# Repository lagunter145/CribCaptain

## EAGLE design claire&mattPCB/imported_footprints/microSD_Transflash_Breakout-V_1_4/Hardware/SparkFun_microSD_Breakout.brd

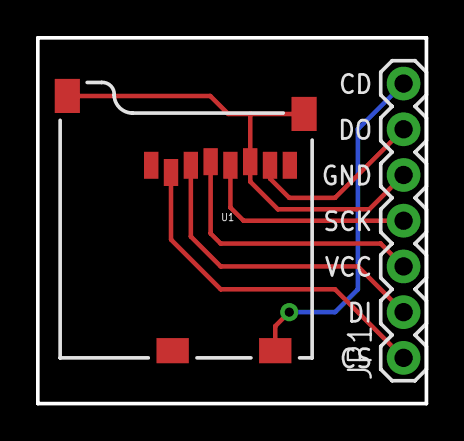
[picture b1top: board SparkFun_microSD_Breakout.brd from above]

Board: 2 copper layers, 21.6 x 20.3 mm, 3 parts (1 on the bottom side), 7 nets.

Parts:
JP1: 1X07
U1: microSD; MICRO-SD-SOCKET-PP
U$1: LOGO-SFENEW; SFE-NEW-WEBLOGO

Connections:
CD1: JP1.7, U1.CD2
CS: JP1.1, U1.2
DI: JP1.2, U1.3
DO: JP1.6, U1.7
GND: JP1.5, U1.6, U1.GND1, U1.GND2
SCK: JP1.4, U1.5
VCC: JP1.3, U1.4

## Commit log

2023-01-18 started pcb kicad project and added stm32 stuff to schematic
2023-01-18 started Eclipse project for code
2023-01-24 3.5 inch display without touch setup included in lcd.c
2023-01-25 t_irq added so that when user touches screen, it registers
2023-01-25 add to gitignore
2023-01-26 schematic for 2.8in touch display with all pins connected
2023-01-27 add language settings xml to gitignore
2023-01-27 Reading from SPI for display's touch
2023-01-30 create rfid files
2023-01-30 basic UART read/write functions, untested.
2023-01-31 copied over functions from Elechouse libraries
2023-02-01 schematics for keypad, lights, 7in display, separate SPI's for 2.8in
2023-02-01 trying different ways to implement touch display's comms on 1 SPI
2023-02-02 changed datatypes of functions
2023-02-03 added back waiting for RXNE bit to read
2023-02-05 SPI-40Pin controller touch added and keypad mod in pcb schematic
2023-02-06 ltspice simulation for sine to square wave converter
2023-02-06 LTSpice simulation for converting a sine to a square wave with same frequency
2023-02-06 wi-fi module, RFID scanner, sineToSquare converter, AC-DC converter
2023-02-06 footprints for IN5822 and RA8875
2023-02-06 removed github repo linking from RA8875 project
2023-02-06 SD Card Reader Schematic
2023-02-07 footprints for SD Card Reader
2023-02-07 4x4 keypad footprint
2023-02-07 linked 4x4 keypad footprint to schematic
2023-02-07 fixed receive() return type to uint
2023-02-08 rounded corner edge cuts and silkscreen for pin labels
2023-02-08 folder for hardware assembly, PN532 V3 RFID model
2023-02-08 2 separate SPI's for 2.8in TFT display and touch
2023-02-08 FillScreen algo adapted from Adafruit RA8775, not init
2023-02-08 minor changes
2023-02-09 initialize display
2023-02-09 ESP8266 footprint and ran electrical check
2023-02-09 organized schematic and separated power supply by modules and our design
2023-02-10 display not working, changed init, testing w arduino
2023-02-10 footprint for barrel jack adapter
2023-02-10 buck rectifier circuit (values wrong), changed how power flags were
2023-02-10 buck converter module cad
2023-02-11 voltage converter module footrints, all components have footprints, BOM
2023-02-11 generated netlist and fixed errors from PCB editing tool
2023-02-14 keypad 3D blueprint
2023-02-14 footprints for every component, pcb footprint layout
2023-02-14 v base casing blueprint
2023-02-14 TPS56325x schematic symbol and footprint
2023-02-15 RA8875 and ESP8266 updated footprints
2023-02-15 added 2.8in tft display in addition to 7in one
2023-02-17 Can read 1 RFID card passively
2023-02-21 micro sd connector schematic/footprint, lm324 footprint
2023-02-22 able to fill screen of display
2023-02-22 updated symbols to include pin names to get rid of ERC warnings
2023-02-22 PCB for 362 development board
2023-02-22 passed ERC and footprints assigned
2023-02-22 moved all 3D files of PCB into hardware assembly folder
2023-02-23 create byte transfer function
2023-02-24 SPI read function working
2023-02-24 initial PCB components, traces laid out with DRC passed
2023-02-24 1:1 footprint changes and layout modded to follow rules
2023-02-25 cleaned up code, touch polling works
2023-02-27 PCB version 2.0
2023-02-28 added text functions
2023-02-28 updated schematic with text descriptions for each block. Also, added 0 ohm resistor and 10 ohm current limiting resistor to pcb. Minor changes were made to the designed buck converter circuit.
2023-02-28 added fantabulous silkscreen names to the board (schmack dab in the middle)
2023-03-01 no DRC warnings
2023-03-08 added oscillator for micro
2023-03-08 added diodes pointing to where 5V outputs
2023-03-08 diodes and vias w labels added
2023-03-10 touch read moved to EXTI interrupt
2023-03-21 last commit before pulling - matthew
2023-03-21 pcb finalization
2023-03-22 wifi: added httprequest function and a semaphore system to timer 6. This will allow there to be delay between different AT commands. timesync: added a basic time system that can be displayed on the 7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
2023-03-24 color changing button!
2023-03-25 wifi: added a more refined http get request that has host header and can now interface with worldclockapi.com. Tried to parse information, but was struggling to read anything being recieved by PA10. 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
2023-03-25 wifi: resolved issue with wifi_getchar
2023-03-28 wifi: finished wifi-time demo (2/27/23) (Matthew and Philip)
2023-03-29 wifi: added second accuracy and fixed it counting to 60 seconds and 60 minutes (Matthew)
2023-03-29 rfid: began to write DMA access info (Matthew)
2023-03-29 wrote simple led main code to test pcb mirco (Matt)
2023-03-30 Add files via upload
    Keypad Stuff
2023-03-31 rfid: using a different module, the new dma code began to work. It works now with one card. The address for th CSELR register was fixed from 0x400202A0 to 0x400200A8 (Matthew and Philip)
2023-04-05 updated to properly read uid's into global array
    disable DMA after receiving a uid packet and writing another command to passive scan for another card. reenable after to prevent the command's ACK frame response from filling the uid buffer.
2023-04-05 working demo for checking off PCB Touch, wifi, timing synch, and display for PSSCS. ManLab 4/5/2023 (Matt)
2023-04-07 wifi: added rudimentary error handling (Matthew)
2023-04-10 removed some artifacts of original library code
2023-04-10 realigned uid extraction in DMA handler
    the DMA buffer will fill with the response preamble, length, checksum, etc.
2023-04-11 removing files from gitignre
2023-04-11 remove .project from gitignore
2023-04-12 added untracked pcb files
2023-04-12 move rfid main into separate file
    so that when merged we don't lose the startup sequence
2023-04-12 added rfid init back to main
2023-04-12 rfid: got demo working for manlab show me a thing. wifi: added error handling for when the wifi disconnects (Philip & Matthew)
2023-04-13 time sync: added deboucing to the PC13 interrupt. hopefully it works. needs to test overnight to see what the error is (Matt)
2023-04-13 gui: added basic menu state machines (Matthew)
2023-04-14 broken code trying to implement states (matt)
2023-04-15 keypad: changed to un-debounced version. made it manipulate colors for GUI. wifi: fixed priorities to get wifi to work again (P-man & M-dawg)
2023-04-15 rfid: integrated rfid fully. gui: added basic checkin menu state (Philip)
2023-04-16 gui: added buttons to increment, decrement, enter the rfid guest check-in. Also refactored a lot of the GUI code to clean that bad boy up. Still lots to clean (mdog)
2023-04-16 check in screen doesn't fully redraw, time can now be toggled to show seconds
2023-04-16 centered text for buttons
2023-04-17 check in and roommate working
2023-04-17 wifi: added wifi connected and time acquired state variables. Also moved the menu draw out of the wifi usart irq to avoid spi interruptions (matty)
2023-04-18 cleaned up comments. moved around global variable declarations so all externs are in header files. (philip)
2023-04-19 ece 362 sd card lab
2023-04-19 more sd card include files
2023-04-19 the header files for the sd card
2023-04-20 can communicate with web server to pull each roommate's data including whether they're checked in, how many guests they have, and their events. updates local structs with this data to display on GUI.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
2023-04-21 chore scheduling, refresh
2023-04-21 wifi: added refresh functions for the wifi to communicate with the server and update the device's local values. gui: added refresh menu and chores (Matt & lauren)
2023-04-21 add display -> server change on chores
2023-04-26 state of the project as of final demo
2023-04-27 final working version with hopefully no more locking up (philip)
